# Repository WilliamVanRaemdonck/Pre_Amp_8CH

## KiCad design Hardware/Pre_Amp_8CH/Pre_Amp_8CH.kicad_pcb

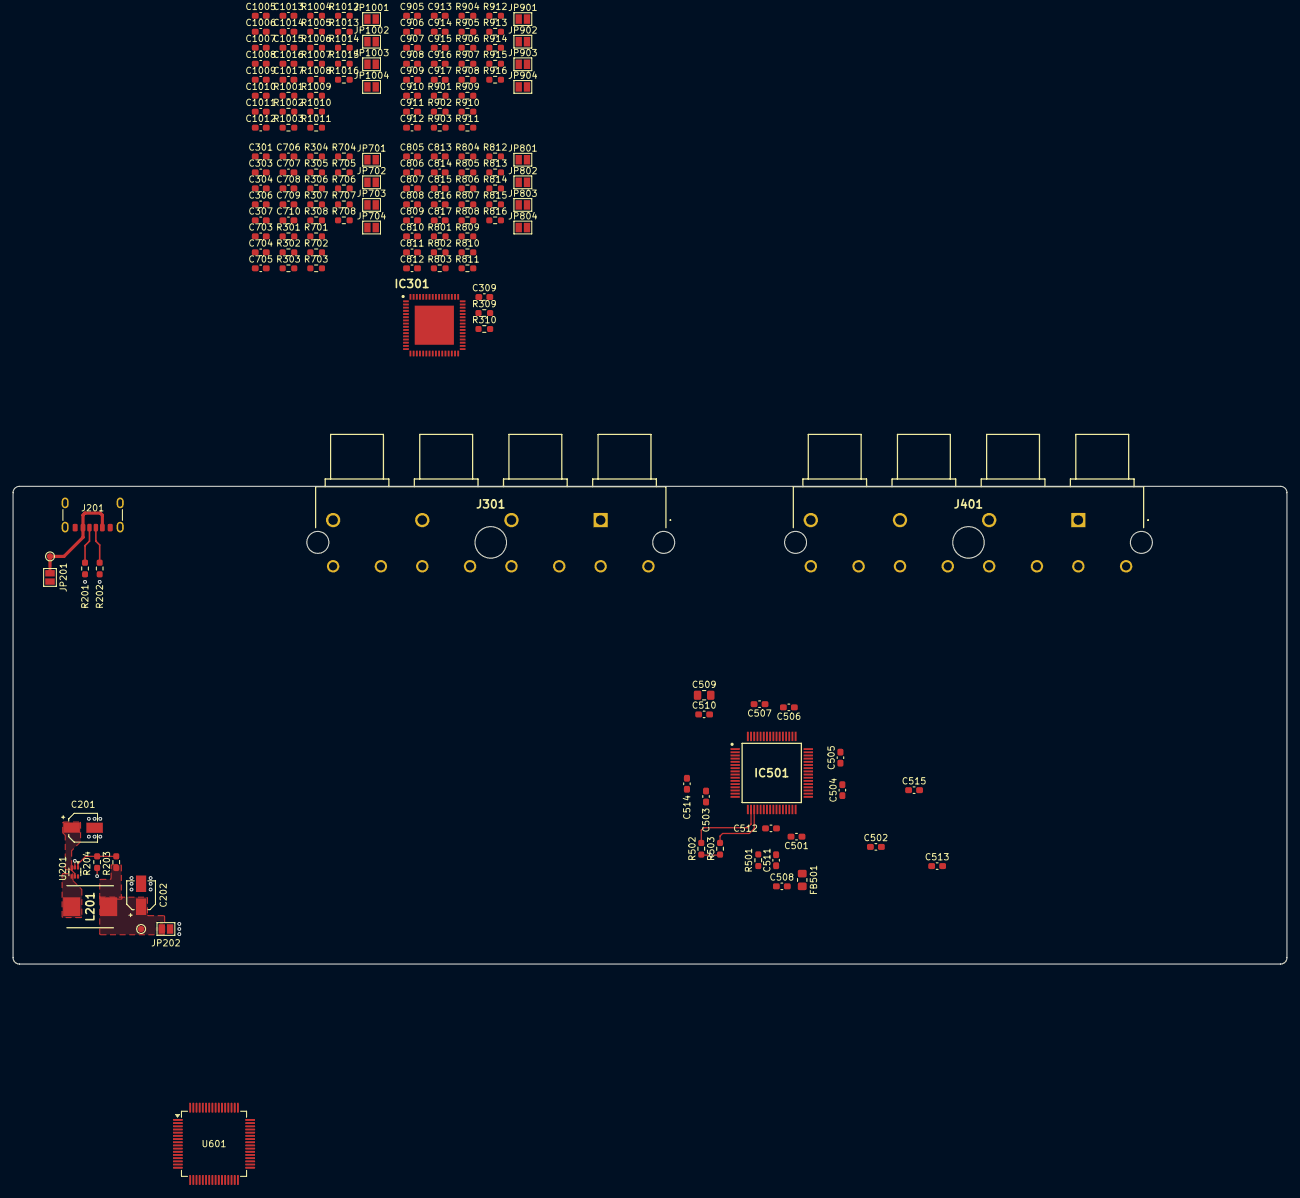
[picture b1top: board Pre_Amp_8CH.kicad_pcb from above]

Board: 4 copper layers, 200.0 x 75.0 mm, 172 parts (0 on the bottom side), 86 nets.

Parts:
C201, C202: 865060240001; CP_Wurth_WCAP-ASLL-D4L5.5
C301, C306, C703, C704, C805, C806, C807, C808, C905, C906, C907, C908, C1005, C1006, C1007, C1008: 1n_film; C_0603_1608Metric_Pad1.08x0.95mm_HandSolder
C303, C307, C511, C512, C705, C706, C809, C810, C811, C812, C909, C910, C911, C912, C1009, C1010, C1011, C1012: 100p; C_0603_1608Metric_Pad1.08x0.95mm_HandSolder
C304, C707, C813, C814, C913, C914, C1013, C1014: 15n_film; C_0603_1608Metric_Pad1.08x0.95mm_HandSolder
C309, C708, C709, C710, C815, C816, C817, C915, C916, C917, C1015, C1016, C1017: 100n; C_0603_1608Metric_Pad1.08x0.95mm_HandSolder
C501, C503, C504, C505, C506, C507, C510, C513: 100nF; C_0603_1608Metric_Pad1.08x0.95mm_HandSolder
C502, C515: 1nF; C_0603_1608Metric_Pad1.08x0.95mm_HandSolder
C508: 1n2; C_0603_1608Metric_Pad1.08x0.95mm_HandSolder
C509: 2u2; C_0805_2012Metric_Pad1.18x1.45mm_HandSolder
C514: 47p; C_0603_1608Metric_Pad1.08x0.95mm_HandSolder
FB501: 600ohm100MHz; R_0805_2012Metric_Pad1.20x1.40mm_HandSolder
IC301: AK5558VN; QFN50P900X900X100-65N
IC501: STA309A13TR; QFP50P1200X1200X160-64N
J201: USB_C_Receptacle_PowerOnly_6P; USB_C_Receptacle_GCT_USB4125-xx-x-0190_6P_TopMnt_Horizontal
J301, J401: PJRAS4X2U01AUX
JP201: USB_jumper; SolderJumper-2_P1.3mm_Open_Pad1.0x1.5mm
JP202: 3V3_jumper; SolderJumper-2_P1.3mm_Open_Pad1.0x1.5mm
JP701, JP702, JP703, JP704, JP801, JP802, JP803, JP804, JP901, JP902, JP903, JP904, JP1001, JP1002, JP1003, JP1004: SolderJumper_2_Open; SolderJumper-2_P1.3mm_Open_Pad1.0x1.5mm
L201: BMRA000606301R0MA1; INDPM7366X300N
R201, R202: 5K1; R_0603_1608Metric_Pad0.98x0.95mm_HandSolder
R203: 453k; R_0603_1608Metric_Pad0.98x0.95mm_HandSolder
R204: 100k; R_0603_1608Metric_Pad0.98x0.95mm_HandSolder
R301, R302, R701, R702, R801, R802, R803, R804, R901, R902, R903, R904, R1001, R1002, R1003, R1004: 4K7; R_0603_1608Metric_Pad0.98x0.95mm_HandSolder
R303, R304, R306, R307, R703, R704, R705, R706, R805, R806, R807, R808, R809, R810, R811, R812, R905, R906, R907, R908, R909, R910, R911, R912, R1005, R1006, R1007, R1008, R1009, R1010, R1011, R1012: 3K3; R_0603_1608Metric_Pad0.98x0.95mm_HandSolder
R305, R308, R707, R708, R813, R814, R815, R816, R913, R914, R915, R916, R1013, R1014, R1015, R1016: 10E; R_0603_1608Metric_Pad0.98x0.95mm_HandSolder
R309, R310, R502, R503: 10K; R_0603_1608Metric_Pad0.98x0.95mm_HandSolder
R501: 3K4; R_0603_1608Metric_Pad0.98x0.95mm_HandSolder
TP201: USB; TestPoint_Pad_D1.0mm
TP202: 3V3; TestPoint_Pad_D1.0mm
U201: TLV62569ADRL; SOT-563
U601: STM32F410R8Tx; LQFP-64_10x10mm_P0.5mm

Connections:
+3V3: C501.1, C503.1, C504.1, C505.1, C506.1, C507.1, C509.1, C510.1, IC501.1 (MVO), IC501.3 (VDD_1), IC501.12 (VDD_2), IC501.28 (VDD_3), IC501.35 (VDD_4), IC501.44 (VDD_5), IC501.52 (VDD_6), IC501.59 (VDD_7), JP202.2 (B), R502.1, R503.1
+5V: C201.1, IC301.2 (AVDD1), IC301.15 (AVDD2), JP201.2 (B), R309.2, U201.3 (VIN), U201.5 (EN)
+15V: C708.1, C709.1, C710.1, C815.1, C816.1, C817.1, C915.1, C916.1, C917.1, C1015.1, C1016.1, C1017.1
-15V: C708.2, C709.2, C710.2, C815.2, C816.2, C817.2, C915.2, C916.2, C917.2, C1015.2, C1016.2, C1017.2
/Audio_DSP/I2C_SCL: IC501.19 (SCL), R503.2
/Audio_DSP/I2C_SDA: IC501.18 (SDA), R502.2
/Audio_DSP/LRCKI: C514.1, IC501.10 (LRCKI)
/Audio_DSP/PLL-Filter: C512.1, IC501.21 (FILTER_PLL), R501.1
/Audio_DSP/PLL-Filter-GND: C508.2, C511.2, C512.2, FB501.1, IC501.23 (GNDA)
/Audio_DSP/POWER_ON_RESET: C502.1, IC501.15 (RESET)
/Audio_DSP/PWDN: C515.1, IC501.64 (PWDN)
/Audio_In/AIN1N: C304.1, C307.1, IC301.60 (AIN1N), JP702.1 (A), JP702.2 (B), R307.2, R308.2
/Audio_In/AIN1P: C303.1, C304.2, IC301.59 (AIN1P), JP701.1 (A), JP701.2 (B), R304.2, R305.2
/Audio_In/AIN2N: C706.1, C707.1, IC301.63 (AIN2N), JP704.1 (A), JP704.2 (B), R706.2, R708.2
/Audio_In/AIN2P: C705.1, C707.2, IC301.64 (AIN2P), JP703.1 (A), JP703.2 (B), R705.2, R707.2
/Audio_In/AIN3N: C810.1, C813.1, IC301.4 (AIN3N), JP802.1 (A), JP802.2 (B), R810.2, R814.2
/Audio_In/AIN3P: C809.1, C813.2, IC301.3 (AIN3P), JP801.1 (A), JP801.2 (B), R809.2, R813.2
/Audio_In/AIN4N: C812.1, C814.1, IC301.7 (AIN4N), JP804.1 (A), JP804.2 (B), R812.2, R816.2
/Audio_In/AIN4P: C811.1, C814.2, IC301.8 (AIN4P), JP803.1 (A), JP803.2 (B), R811.2, R815.2
/Audio_In/AIN5N: C910.1, C913.1, IC301.10 (AIN5N), JP902.1 (A), JP902.2 (B), R910.2, R914.2
/Audio_In/AIN5P: C909.1, C913.2, IC301.9 (AIN5P), JP901.1 (A), JP901.2 (B), R909.2, R913.2
/Audio_In/AIN6N: C912.1, C914.1, IC301.13 (AIN6N), JP904.1 (A), JP904.2 (B), R912.2, R916.2
/Audio_In/AIN6P: C911.1, C914.2, IC301.14 (AIN6P), JP903.1 (A), JP903.2 (B), R911.2, R915.2
/Audio_In/AIN7N: C1010.1, C1013.1, IC301.18 (AIN7N), JP1002.1 (A), JP1002.2 (B), R1010.2, R1014.2
/Audio_In/AIN7P: C1009.1, C1013.2, IC301.17 (AIN7P), JP1001.1 (A), JP1001.2 (B), R1009.2, R1013.2
/Audio_In/AIN8N: C1012.1, C1014.1, IC301.21 (AIN8N), JP1004.1 (A), JP1004.2 (B), R1012.2, R1016.2
/Audio_In/AIN8P: C1011.1, C1014.2, IC301.22 (AIN8P), JP1003.1 (A), JP1003.2 (B), R1011.2, R1015.2
/Audio_In/BIAS: C309.1, R309.1, R310.2
/Audio_In/IN1L: J301.T11, R301.1
/Audio_In/IN1R: J301.T12, R701.1
/Audio_In/IN2L: J301.T21, R801.1
/Audio_In/IN2R: J301.T22, R802.1
/Audio_In/IN3L: J301.T31, R901.1, R902.1
/Audio_In/IN4L: J301.T41, R1001.1
/Audio_In/IN4R: J301.T42, R1002.1
/PSU/3V3_sb: C202.1, JP202.1 (A), L201.2, R203.1, TP202.1
/PSU/CC1: J201.A5 (CC1), R202.1
/PSU/CC2: J201.B5 (CC2), R201.1
/PSU/FB: R203.2, R204.1, U201.1 (FB)
/PSU/SW: L201.1, U201.4 (SW)
/PSU/VBUS: J201.A9 (VBUS), J201.B9 (VBUS), JP201.1 (A), TP201.1
GNDA: C303.2, C307.2, C309.2, C705.2, C706.2, C809.2, C810.2, C811.2, C812.2, C909.2, C910.2, C911.2, C912.2, C1009.2, C1010.2, C1011.2, C1012.2, IC301.1 (AVSS1), IC301.16 (AVSS2), J301.S1, J301.S2, J301.S3, J301.S4, R310.1
GNDD: C201.2, C202.2, C501.2, C502.2, C503.2, C504.2, C505.2, C506.2, C507.2, C509.2, C510.2, C513.2, C514.2, C515.2, FB501.2, IC501.2 (GND_1), IC501.4 (GND_2), IC501.13 (GND_3), IC501.16 (PLLB), IC501.17 (SA), IC501.27 (GND_4), IC501.36 (GND_5), IC501.45 (GND_6), IC501.53 (GND_7), IC501.60 (GND_8), J201.A12 (GND), J201.B12 (GND), J201.S1 (SHIELD), R201.2, R202.2, R204.2, U201.2 (GND)
unnamed: C301.2, R305.1
unnamed: C306.2, R308.1
unnamed: C508.1, C511.1, R501.2
unnamed: C703.2, R707.1
unnamed: C704.2, R708.1
unnamed: C805.2, R813.1
unnamed: C806.2, R814.1
unnamed: C807.2, R815.1
unnamed: C808.2, R816.1
unnamed: C905.2, R913.1
unnamed: C906.2, R914.1
unnamed: C907.2, R915.1
unnamed: C908.2, R916.1
unnamed: C1005.2, R1013.1
unnamed: C1006.2, R1014.1
unnamed: C1007.2, R1015.1
unnamed: C1008.2, R1016.1
unnamed: C513.1, IC501.24 (VDDA)
unnamed: U601.18 (VSS), U601.31 (VSS), U601.47 (VSS), U601.63 (VSS)
unnamed: R301.2, R302.1
unnamed: C301.1, R303.2, R304.1
unnamed: C306.1, R306.2, R307.1
unnamed: C704.1, R704.2, R706.1
unnamed: R701.2, R702.1
unnamed: C703.1, R703.2, R705.1
unnamed: R801.2, R803.1
unnamed: C805.1, R805.2, R809.1
unnamed: R802.2, R804.1
unnamed: C807.1, R807.2, R811.1
unnamed: C806.1, R806.2, R810.1
unnamed: C808.1, R808.2, R812.1
unnamed: R901.2, R903.1
unnamed: C905.1, R905.2, R909.1
unnamed: R902.2, R904.1
unnamed: C907.1, R907.2, R911.1
unnamed: C906.1, R906.2, R910.1
unnamed: C908.1, R908.2, R912.1
unnamed: R1001.2, R1003.1
unnamed: C1005.1, R1005.2, R1009.1
unnamed: R1002.2, R1004.1
unnamed: C1007.1, R1007.2, R1011.1
unnamed: C1006.1, R1006.2, R1010.1
unnamed: C1008.1, R1008.2, R1012.1

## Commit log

2025-08-27 Init hardware Kicad V9.0
2025-08-27 init schematic
2025-08-27 RCA in & OUT
2025-08-27 DSP start
2025-08-29 audio input buffers
